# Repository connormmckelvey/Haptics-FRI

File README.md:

# Haptics-FRI

Haptics-FRI is a wearable vibrotactile feedback system developed in the UT Austin Human Enabled Robotics Lab (HERL) for the Freshman Research Initiative (FRI) stream. The project explores how lightweight haptic cues can support motor learning and robotic teleoperation.

At a system level, a host computer sends motor activation commands to a USB dongle, the dongle relays those commands over ESP-NOW to a wearable band, and the band drives four vibration motors after remapping commands based on wrist orientation from an IMU.

## Project Goals

- Build a low-latency, wireless haptic communication loop
- Provide intuitive directional feedback using a 4-motor wearable band
- Keep feedback aligned to the user's physical orientation using IMU-based remapping
- Support rapid prototyping from both embedded firmware and host-side Python tools

## System Architecture

PC -> USB Serial -> Dongle (ESP32-C3) -> ESP-NOW -> Band (ESP32-C3 + MPU6050 + motor driver) -> 4 haptic motors

## Repository Structure

- firmware/: PlatformIO project for embedded firmware, protocol types, and test tooling
- firmware/src/dongle.cpp: Active dongle firmware (serial-to-ESP-NOW bridge)
- firmware/excluded_src/band.cpp: Band firmware (IMU-aware motor remapping and motor control)
- firmware/include/packet_types.h: Shared packet and IMU data structures
- firmware/tools/test_send_mtr_cmd.py: Python utility that sends random 4-byte motor packets
- masterpod_pcb_kicad/: KiCad design files and Gerber outputs for the wearable board
- software/Pose.py: MoveNet-based wrist tracking prototype for vision-driven haptic logic
- software/how_to_send_mtr_cmds.md: Serial packet protocol reference for host applications

## Hardware and Firmware

### Hardware

- 2x Seeed XIAO ESP32-C3 (dongle and band)
- MPU6050 IMU on band
- ULN2003A motor driver
- 4 haptic motors arranged as top/right/bottom/left
- External antenna recommended for reliable ESP-NOW range

### Firmware Responsibilities

- Dongle firmware:
	- Reads raw 4-byte motor commands from USB serial at 115200 baud
	- Forwards commands to the band via ESP-NOW
	- Tracks send success/failure on serial logs

- Band firmware:
	- Receives motor commands over ESP-NOW
	- Reads IMU orientation
	- Remaps motor indices to preserve directional meaning relative to wrist orientation
	- Drives motor output pins

### Packet Format

Each command is exactly 4 bytes:

- Byte 0: top motor
- Byte 1: right motor
- Byte 2: bottom motor
- Byte 3: left motor

Each byte is 0 (off) or 1 (on).

## Software Components

### Host Command Interface

- software/how_to_send_mtr_cmds.md documents the serial protocol
- firmware/tools/test_send_mtr_cmd.py provides a quick motor-command generator for validation

### Computer Vision Prototype

- software/Pose.py runs MoveNet (TensorFlow Hub) on webcam frames
- Detects wrist keypoints and demonstrates where haptic feedback logic can plug in
- Current feedback hook prints decisions; it is not yet wired to serial transmission

## Getting Started

### 1. Clone the repository

```bash
git clone https://github.com/connormmckelvey/Haptics-FRI
cd Haptics-FRI
```

### 2. Firmware setup (PlatformIO)

The firmware project is configured in firmware/platformio.ini for seeed_xiao_esp32c3.

From the firmware directory:

```bash
platformio run
platformio run --target upload
platformio device monitor -b 115200
```

Notes:

- The active source in firmware/src is the dongle firmware.
- Band firmware currently lives in firmware/excluded_src/band.cpp and is not in the default build path.
- Ensure dongle and band use the same ESP-NOW channel.
- Update the hardcoded band MAC address in firmware/src/dongle.cpp when changing hardware.

### 3. Python tooling setup

For motor command testing:

```bash
pip install pyserial
python firmware/tools/test_send_mtr_cmd.py
```

For vision prototype (software/Pose.py):

```bash
pip install opencv-python numpy tensorflow tensorflow-hub
python software/Pose.py
```

## Engineering Notes

- IMU calibration is performed at band startup; keep the device still during calibration.
- The serial command path uses raw bytes without framing, acknowledgements, or checksums.
- If packets stop midway, dongle firmware resets partial serial reads after a short timeout.

## Current Status and Known Gaps

- Root-level documentation is now expanded, but some subsystem docs are still in-progress.
- software/cv_docs.md is currently empty.
- Pose-to-haptics closed-loop integration is not complete yet.
- Band firmware is stored under excluded_src and may need project reconfiguration for direct builds.

## Suggested Next Milestones

1. Promote band firmware into an actively built PlatformIO target.
2. Add requirements files for reproducible Python environments.
3. Implement serial output from software/Pose.py into the 4-byte dongle protocol.
4. Add repeatable validation tests for motor mapping and IMU remapping behavior.

## Acknowledgment

This project was created in the UT Austin Freshman Research Initiative within the Human Enabled Robotics Lab (HERL), with the goal of combining embedded systems, wearable haptics, and human-robot interaction research.

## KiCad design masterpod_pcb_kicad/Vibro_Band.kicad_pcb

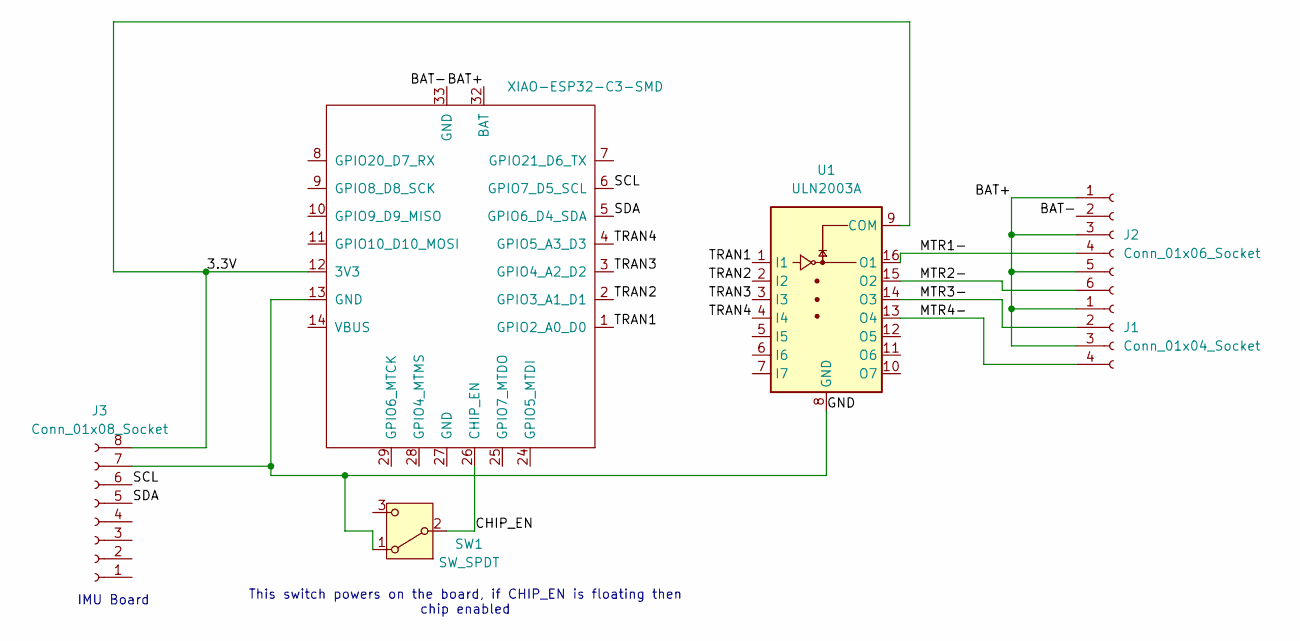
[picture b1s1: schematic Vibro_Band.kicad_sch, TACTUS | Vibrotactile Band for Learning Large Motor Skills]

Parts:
J1: Conn_01x04_Socket; PinSocket_1x04_P2.54mm_Horizontal
J2: Conn_01x06_Socket; PinSocket_1x06_P2.54mm_Horizontal
J3: Conn_01x08_Socket; PinSocket_1x08_P2.54mm_Horizontal
SW1: SW_SPDT; SW_Slide_SPDT_Angled_CK_OS102011MA1Q
U1: ULN2003A; DIP-16_W7.62mm
U3: XIAO-ESP32-C3-SMD

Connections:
/3.3V: J3.8, U1.9 (COM), U3.12 (3V3)
/BAT+: J1.1, J1.3, J2.1, J2.3, J2.5, U3.32 (BAT)
/BAT-: J2.2, U3.33 (GND)
/CHIP_EN: SW1.2 (B), U3.26 (CHIP_EN)
/GND: J3.7, SW1.1 (A), U1.8 (GND), U3.13 (GND)
/MTR1-: J2.4, U1.16 (O1)
/MTR2-: J2.6, U1.15 (O2)
/MTR3-: J1.2, U1.14 (O3)
/MTR4-: J1.4, U1.13 (O4)
/SCL: J3.6, U3.6 (GPIO7_D5_SCL)
/SDA: J3.5, U3.5 (GPIO6_D4_SDA)
/TRAN1: U1.1 (I1), U3.1 (GPIO2_A0_D0)
/TRAN2: U1.2 (I2), U3.2 (GPIO3_A1_D1)
/TRAN3: U1.3 (I3), U3.3 (GPIO4_A2_D2)
/TRAN4: U1.4 (I4), U3.4 (GPIO5_A3_D3)

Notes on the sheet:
This switch powers on the board, if CHIP_EN is floating then chip enabled
IMU Board

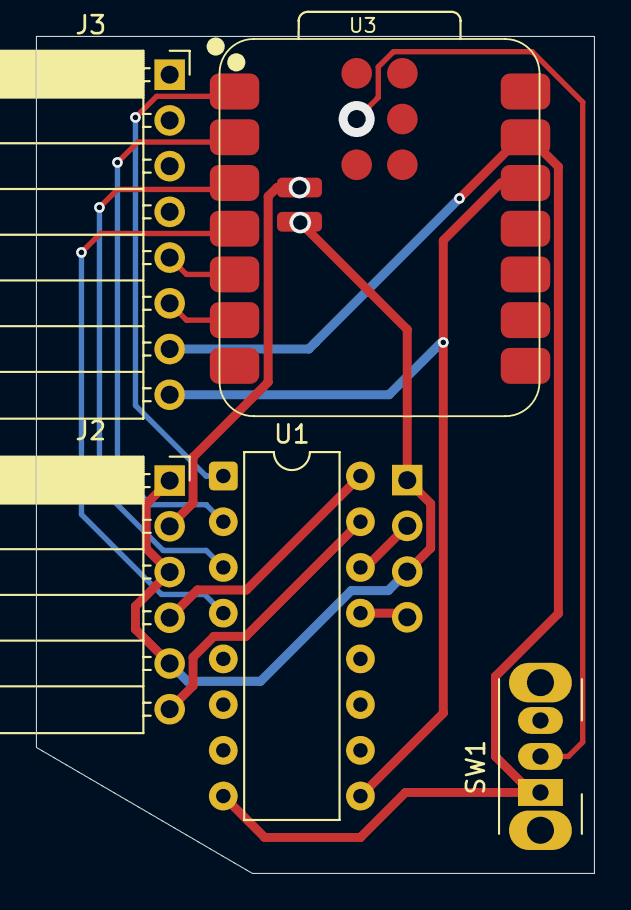
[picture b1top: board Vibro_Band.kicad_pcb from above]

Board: 2 copper layers, 31.0 x 46.5 mm, 6 parts (1 on the bottom side), 15 nets.

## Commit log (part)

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2026-03-24 setup firmware directory
2026-04-01 added cv docs
2026-04-02 set up structure and coded out espnow protocol and datastructure. missing IMU implementation
2026-04-02 Update README with git usage instructions
    Added git commands for cloning and managing the repository.
2026-04-06 hi this is a test
2026-04-07 added kicad files
2026-04-08 band working to test motor with new ULN2003a Driver
2026-04-08 Starting pose estimation code
2026-04-09 v1 working esp_now with sending dummy motor commands, pins switching correctly. only missing IMU implementation
2026-04-09 updates to packet struct and implemented imu rotation NOT TESTED
2026-04-09 v1_firmware_complete
2026-04-09 added markdown file for ralph and chris to understand serial cmds
2026-04-09 added firmware readme
2026-04-11 finished pcb?
2026-04-13 pcb updates
2026-04-13 new pcb updates
2026-04-18 updates to kicad
2026-04-19 working IMU feedback!
2026-04-26 pose code update
2026-04-26 only tracking right wrist
2026-04-26 zone designer + pose estimation code update
2026-04-27 mirrored camera issue fix
2026-05-02 comment changes
